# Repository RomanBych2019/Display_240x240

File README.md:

# Display 240x240

Прошивка дисплея 240x240 для системы CNG/EVO на базе ESP32-C3. Устройство читает данные автомобиля и газового блока по CAN, отображает телеметрию на TFT-дисплее, рассчитывает показатели экономичного вождения и поднимает локальный Wi-Fi веб-портал для просмотра параметров, настройки страниц дисплея, загрузки файлов и OTA-обновления.

## Возможности

- Прием CAN-данных EVO и J1939: обороты, скорость, пробег, расход ДТ, температуры, нагрузка двигателя, вес автомобиля, параметры CNG.
- Отображение страниц на круглом/квадратном TFT 240x240: CNG, параметры EVO, кнопка газ/ДТ, уровень топлива, соленоиды, потеря связи с EVO.
- Переключение пользовательских страниц жестами тач-контроллера CST816D.
- Долгое нажатие на странице кнопки газ/ДТ отправляет CAN-команду включения/выключения газа.
- Расчет уровня экономичного вождения по карте `ACC/RPM`.
- Расчет среднего расхода газа и примерного остаточного пробега.
- Веб-портал в режиме Wi-Fi AP для телеметрии и настроек.
- OTA-обновление через GyverPortal.
- Контроль перегрева ESP32: при высокой температуре снижается мощность Wi-Fi, частота обновления и яркость дисплея.

## Аппаратная платформа

- MCU: `ESP32-C3 DevKitM-1`
- Framework: Arduino
- Дисплей: TFT 240x240, драйвер `GC9A01`, библиотека `TFT_eSPI`
- Тач-контроллер: `CST816D`
- CAN: TWAI ESP32-C3, библиотека `ESP32-TWAI-CAN`
- Файловая система: `LittleFS`

### Основные пины

| Узел | Сигнал | GPIO |
| --- | --- | --- |
| CAN | RX | `GPIO20` |
| CAN | TX | `GPIO21` |
| Touch I2C | SDA | `GPIO4` |
| Touch I2C | SCL | `GPIO5` |
| Touch | INT | `GPIO0` |
| Touch | RST | `GPIO1` |
| TFT SPI | MOSI | `GPIO7` |
| TFT SPI | SCLK | `GPIO6` |
| TFT | CS | `GPIO10` |
| TFT | DC | `GPIO2` |
| TFT | BL | `GPIO3` |
| TFT | RST | `-1` |

Пины TFT задаются в локальной копии библиотеки: `lib/TFT_eSPI-master/User_Setup.h`.

## Сборка и прошивка

Проект собирается через PlatformIO.

```bash
pio run
```

Загрузка прошивки:

```bash
pio run --target upload
```

Загрузка файлов LittleFS из папки `data/`:

```bash
pio run --target uploadfs
```

Монитор порта:

```bash
pio device monitor
```

Основное окружение PlatformIO:

- `env:esp32-c3-devkitm-1`
- `platform = espressif32@5.3.0`
- `board = esp32-c3-devkitm-1`
- `framework = arduino`
- `board_build.partitions = partition.csv`
- `board_build.filesystem = littlefs`
- `monitor_speed = 115200`
- USB CDC включен на старте через `ARDUINO_USB_CDC_ON_BOOT=1`

## Wi-Fi и веб-портал

После запуска устройство поднимает точку доступа:

- SSID: `DisplayEVO`
- Пароль: `00000001`

Веб-портал построен на `GyverPortal`. Через него доступны:

- вкладка телеметрии автомобиля и EVO;
- выбор скорости CAN-шины;
- выбор типа автомобиля;
- настройка объема газовых баллонов;
- включение/отключение страниц дисплея;
- загрузка карты `Map_ACC-RPM.csv`;
- OTA-обновление.

Данные для OTA:

- Логин: `ItalGaz`
- Пароль: `001`

## Файлы LittleFS

Содержимое папки `data/` загружается во flash-файловую систему устройства.

| Файл | Назначение |
| --- | --- |
| `Map_ACC-RPM.csv` | Карта оценки экономичности по педали ACC и RPM |
| `Error_EVO_new.csv` | Справочник ошибок EVO |
| `screen*.png` | PNG-экраны/графика для отображения |
| `display_config.json` | Настройки дисплея и автомобиля, создаются/обновляются прошивкой |

Если `display_config.json` отсутствует, прошивка использует значения по умолчанию из `src/main.cpp` и `src/can_settings.h`.

## CAN-данные

Прошивка принимает расширенные CAN-кадры EVO и стандартные J1939 PGN автомобиля. Основные идентификаторы описаны в `src/can_settings.h`.

### Входящие EVO

| ID | Назначение |
| --- | --- |
| `0x18FFF0BB` | состояние газ/ДТ, ACC, впрыск газа, давление, температуры |
| `0x18FFF1BB` | уровень CNG и температура редуктора |
| `0x18FFFBBB` | ошибки EVO и версия |
| `0x18FFF8BB` | расход газа за поездку и общий расход |
| `0x18FFFAA1` | состояние и токи соленоидов |
| `0x18FFFBA1` | уровень дизельного топлива |

### Входящие J1939

| PGN | Назначение |
| --- | --- |
| `0xFEF1` | скорость автомобиля |
| `0xFEC1` | пробег |
| `0xFEF2` | мгновенный расход ДТ |
| `0xF004` | обороты и нагрузка двигателя |
| `0xFEF6` | температуры воздуха/выхлопа |
| `0xFEEE` | температуры ОЖ, масла, топлива |
| `0xFEEA` | вес автомобиля |

### Исходящие CAN

| ID | Назначение |
| --- | --- |
| `0x18FFEEDD` | команда включения/выключения газа |
| `0x18FFFEDD` | диагностические данные дисплея: экономичность, средний расход, запас хода, объем баллонов |

## Структура проекта

```text
.
├── data/                  # файлы LittleFS
├── display/               # графические исходники дисплея
├── docs/                  # документация, схемы, платы, даташиты
├── include/               # стандартная папка PlatformIO
├── lib/                   # локальные библиотеки проекта
├── src/                   # исходный код прошивки
├── test/                  # стандартная папка PlatformIO
├── platformio.ini         # настройки сборки
├── partition.csv          # разметка flash
├── max_app_4MB.csv        # альтернативная разметка
└── min_spiffs.csv         # альтернативная разметка
```

Ключевые файлы в `src/`:

- `main.cpp`, `main.h` - запуск, задачи FreeRTOS, обработка CAN, расчеты, LittleFS-настройки.
- `TFT_240_240.cpp`, `TFT_240_240.h` - отрисовка страниц TFT-дисплея.
- `WebPortal.cpp`, `WebPortal.h` - Wi-Fi AP, веб-интерфейс, OTA, загрузка файлов.
- `CST816D.cpp`, `CST816D.h` - работа с тач-контроллером.
- `can_settings.h` - структура CAN-данных и PGN/ID.
- `DisplayConfig.h` - описание страниц дисплея.
- `PNG_FS_Support.cpp`, `PNG_FS_Support.h` - вывод PNG из файловой системы.
- `SolenoidHealth.h` - состояния соленоидов.

## Локальные библиотеки

В проекте используются локальные копии библиотек:

- `lib/TFT_eSPI-master`
- `lib/PNGdec-master`
- `lib/ESP32-TWAI-CAN-master`

Также через `platformio.ini` подтягиваются:

- `gyverlibs/GyverPortal@^3.6.6`
- `bblanchon/ArduinoJson`

## Настройка страниц дисплея

Начальная конфигурация страниц задается в `src/main.cpp` в объекте `g_displayConfig`.

Доступные страницы:

- `CNG`
- `Параметры EVO`
- `Кнопка газ/дт`
- `Уровень топлива`
- `Соленоиды`
- `EVO Lost`

Веб-портал может включать и отключать пользовательские страницы. Системная страница `EVO Lost` используется для индикации потери связи с газовым блоком.

## Документация

Папка `docs/` содержит схемы, KiCad-проект платы, даташиты и инструкции. Наиболее полезные материалы:

- `docs/Инструкция.pdf`
- `docs/Инструкция карты.pdf`
- `docs/KiCad - TTF 240х240/`
- `docs/SPEC LH128R-IG01 VER A.pdf`
- `docs/esp32-c3_datasheet_en.pdf`

## Примечания для разработки

- Перед проверкой работы на устройстве прошивайте и firmware, и LittleFS.
- При изменении пинов дисплея правьте `lib/TFT_eSPI-master/User_Setup.h`.
- При изменении формата CAN-данных сначала обновляйте `src/can_settings.h`, затем парсинг в `analise_can_id()`.
- Для настройки жестов не удаляйте лог `Touch: x=..., y=..., gesture=...` в `src/main.cpp`: он нужен для проверки координат и распознавания жестов.
- В репозитории есть `.DS_Store` и `Thumbs.db`; они не нужны для сборки.

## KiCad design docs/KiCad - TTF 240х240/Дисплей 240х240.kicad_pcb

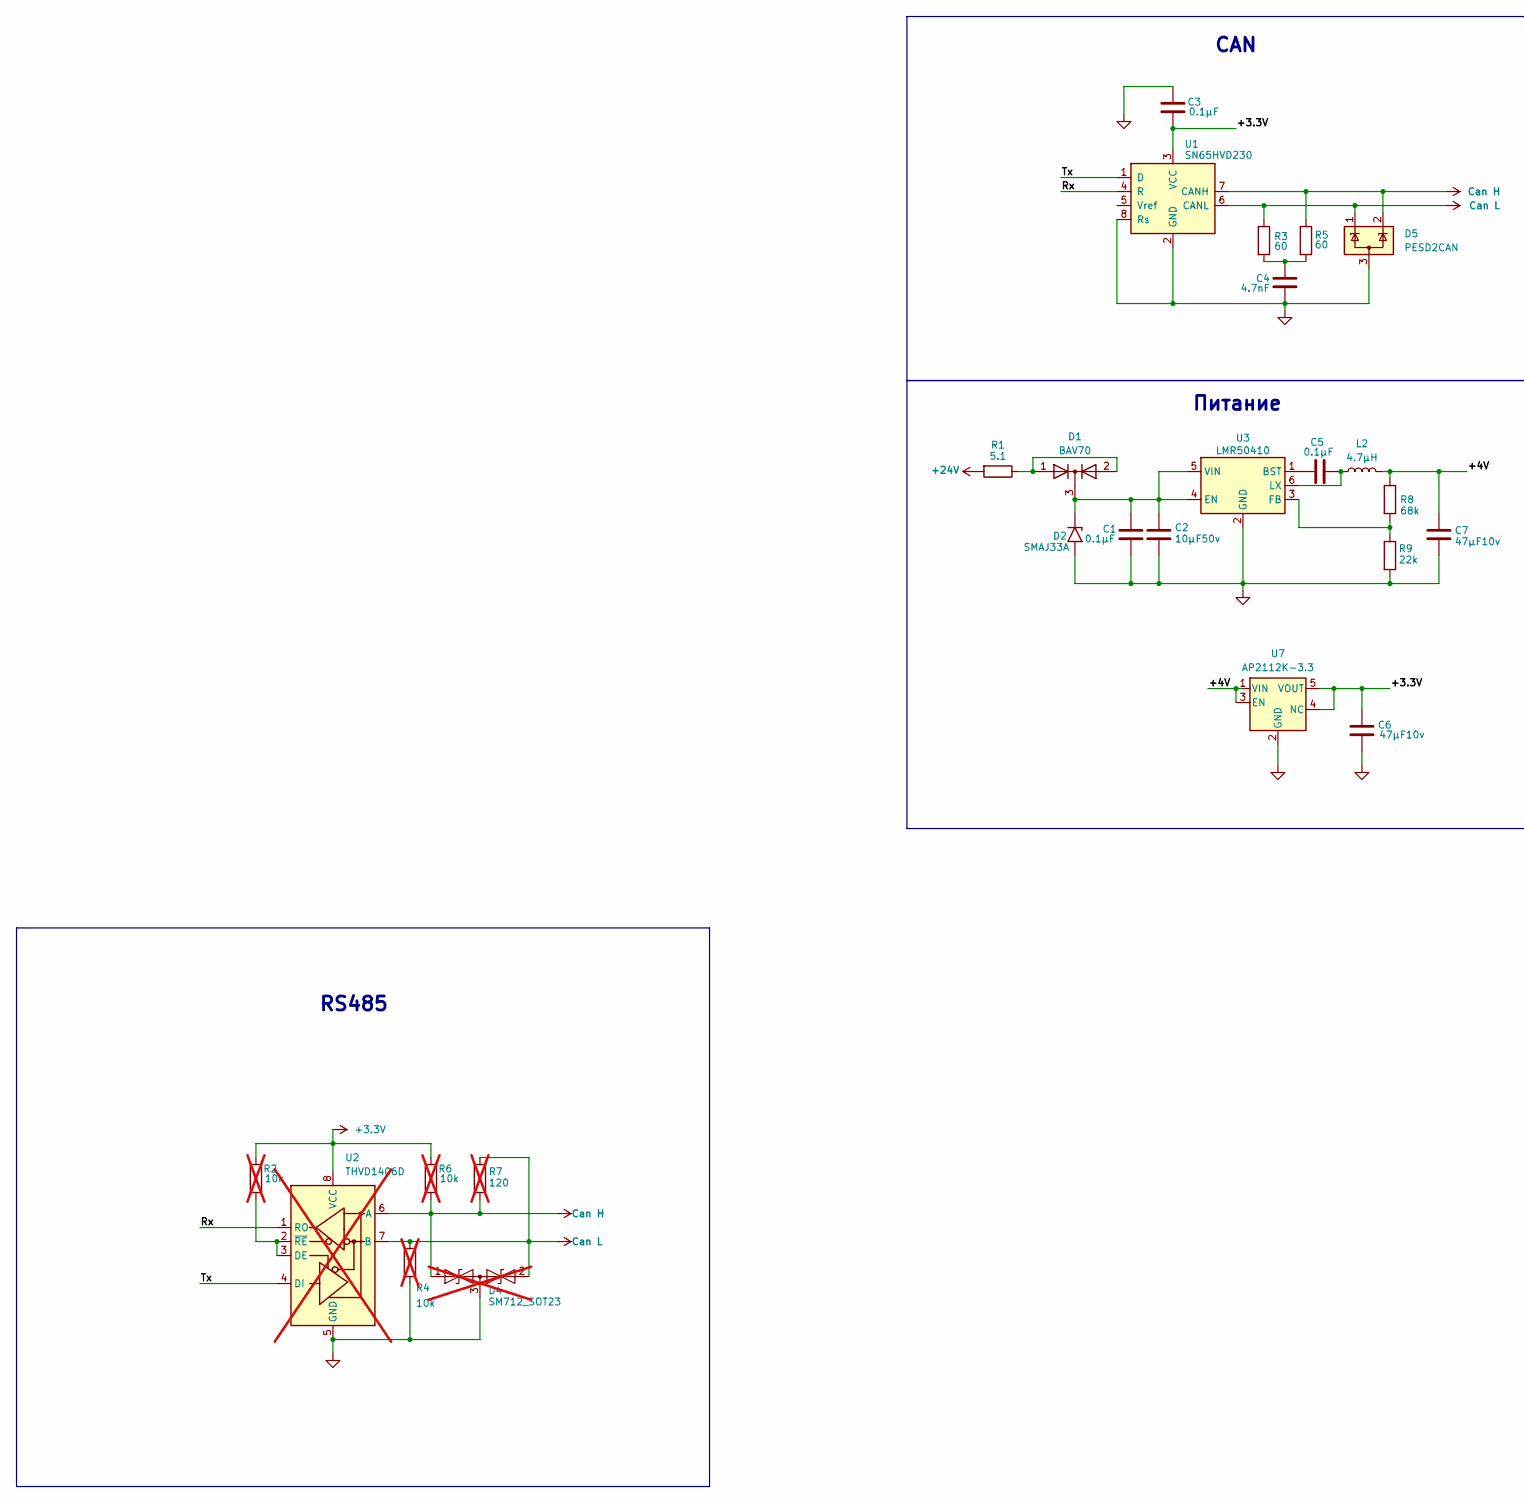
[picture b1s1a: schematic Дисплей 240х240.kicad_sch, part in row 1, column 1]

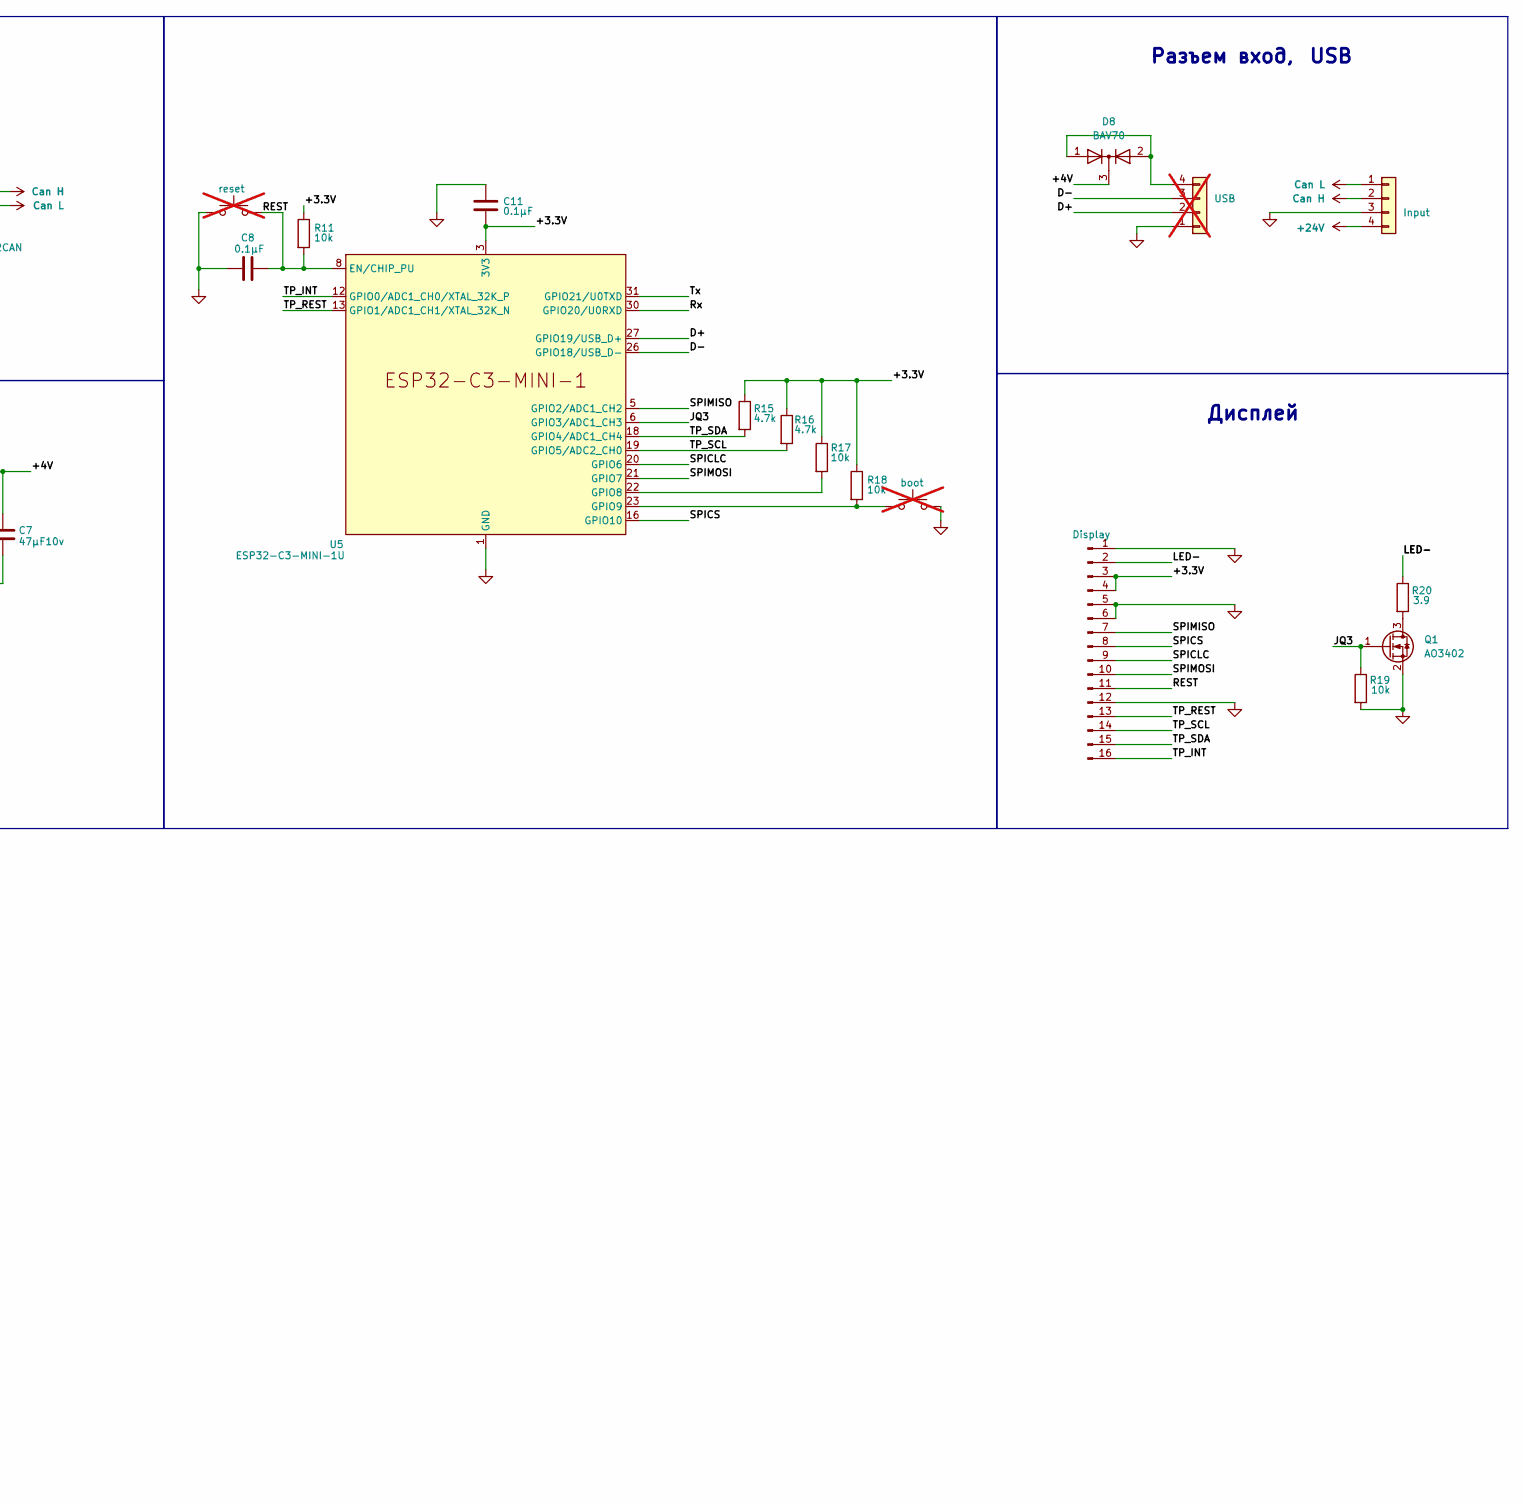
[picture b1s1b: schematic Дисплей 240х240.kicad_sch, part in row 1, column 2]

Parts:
C1, C3, C5, C8, C11: 0.1µF; C_0603_1608Metric
C2: 10µF50v; C_0805_2012Metric
C4: 4.7nF; C_0603_1608Metric
C6, C7: 47µF10v; C_0805_2012Metric
D1, D8: BAV70; SOT-23
D2: SMAJ33A; D_SMA
D4: SM712_SOT23; SOT-23; not fitted
D5: PESD2CAN; SOT-23
J1: Display; ER-OLED0.42
J2: USB; PinHeader_1x04_P2.54mm_Vertical; not fitted
J3: Input; JST_GH_BM04B-GHS-TBT_1x04-1MP_P1.25mm_Vertical
L2: 4.7µH; L_1210_3225Metric
Q1: AO3402; SOT-23
R1: 5.1; R_0805_2012Metric
R2, R4, R6: 10k; R_0603_1608Metric; not fitted
R3, R5: 60; R_0603_1608Metric
R7: 120; R_0603_1608Metric; not fitted
R8: 68k; R_0603_1608Metric
R9: 22k; R_0603_1608Metric
R11, R17, R18, R19: 10k; R_0603_1608Metric
R15, R16: 4.7k; R_0603_1608Metric
R20: 3.9; R_0603_1608Metric
SW1: reset; SW_SPST_B3U-1000P; not fitted
SW2: boot; SW_SPST_B3U-1000P; not fitted
U1: SN65HVD230; SOIC-8_3.9x4.9mm_P1.27mm
U2: THVD1406D; SOIC-8_3.9x4.9mm_P1.27mm; not fitted
U3: LMR50410; SOT-23-6
U5: ESP32-C3-MINI-1U
U7: AP2112K-3.3; SOT-23-5

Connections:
+3.3V: C3.1, C6.1, C11.1, J1.3, J1.4, R2.1, R6.1, R11.1, R15.1, R16.1, R17.1, R18.1, U1.3 (VCC), U2.8 (VCC), U5.3 (3V3), U7.4 (NC), U7.5 (VOUT)
+24V: J3.4, R1.2
/+4V: C7.1, D8.3 (K), L2.2, R8.1, U7.1 (VIN), U7.3 (EN)
/<NO NET>: U1.1 (D), U1.4 (R), U2.1 (RO), U2.4 (DI), U5.30 (GPIO20/U0RXD), U5.31 (GPIO21/U0TXD)
/D+: J2.2, U5.27 (GPIO19/USB_D+)
/D-: J2.3, U5.26 (GPIO18/USB_D-)
/JQ3: Q1.1 (G), R19.1, U5.6 (GPIO3/ADC1_CH3)
/LED-: J1.2, R20.1
/REST: C8.1, J1.11, R11.2, SW1.2, U5.8 (EN/CHIP_PU)
/SPICLC: J1.9, U5.20 (GPIO6)
/SPICS: J1.8, U5.16 (GPIO10)
/SPIMISO: J1.7, U5.5 (GPIO2/ADC1_CH2)
/SPIMOSI: J1.10, U5.21 (GPIO7)
/TP_INT: J1.16, U5.12 (GPIO0/ADC1_CH0/XTAL_32K_P)
/TP_REST: J1.13, U5.13 (GPIO1/ADC1_CH1/XTAL_32K_N)
/TP_SCL: J1.14, R16.2, U5.19 (GPIO5/ADC2_CH0)
/TP_SDA: J1.15, R15.2, U5.18 (GPIO4/ADC1_CH4)
Can H: D4.1 (A1), D5.2 (K), J3.2, R5.1, R6.2, R7.2, U1.7 (CANH), U2.6 (A)
Can L: D4.2 (A2), D5.1 (K), J3.1, R3.1, R4.1, R7.1, U1.6 (CANL), U2.7 (B)
GND: C1.2, C2.2, C3.2, C4.1, C6.2, C7.2, C8.2, C11.2, D2.2 (A2), D4.3 (common), D5.3 (A), J1.1, J1.5, J1.6, J1.12, J2.1, J3.3, Q1.2 (S), R4.2, R9.2, R19.2, SW1.1, SW2.2, U1.2 (GND), U1.8 (Rs), U2.5 (GND), U3.2 (GND), U5.1 (GND), U5.2 (GND), U5.11 (GND), U5.14 (GND), U5.36 (GND), U5.37 (GND), U5.38 (GND), U5.39 (GND), U5.40 (GND), U5.41 (GND), U5.42 (GND), U5.43 (GND), U5.44 (GND), U5.45 (GND), U5.46 (GND), U5.47 (GND), U5.48 (GND), U5.49 (GND), U5.50 (GND), U5.51 (GND), U5.52 (GND), U5.53 (GND), U7.2 (GND)
unnamed: C4.2, R3.2, R5.2
unnamed: D1.1 (A), D1.2 (A), R1.1
unnamed: C1.1, C2.1, D1.3 (K), D2.1 (A1), U3.4 (EN), U3.5 (VIN)
unnamed: D8.1 (A), D8.2 (A), J2.4
unnamed: Q1.3 (D), R20.2
unnamed: R2.2, U2.2 (~RE), U2.3 (DE)
unnamed: C5.2, U3.1 (BST)
unnamed: R8.2, R9.1, U3.3 (FB)
unnamed: C5.1, L2.1, U3.6 (LX)
unnamed: R17.2, U5.22 (GPIO8)
unnamed: R18.2, SW2.1, U5.23 (GPIO9)

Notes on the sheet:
Питание
Дисплей
CAN
RS485
Разъем вход, USB

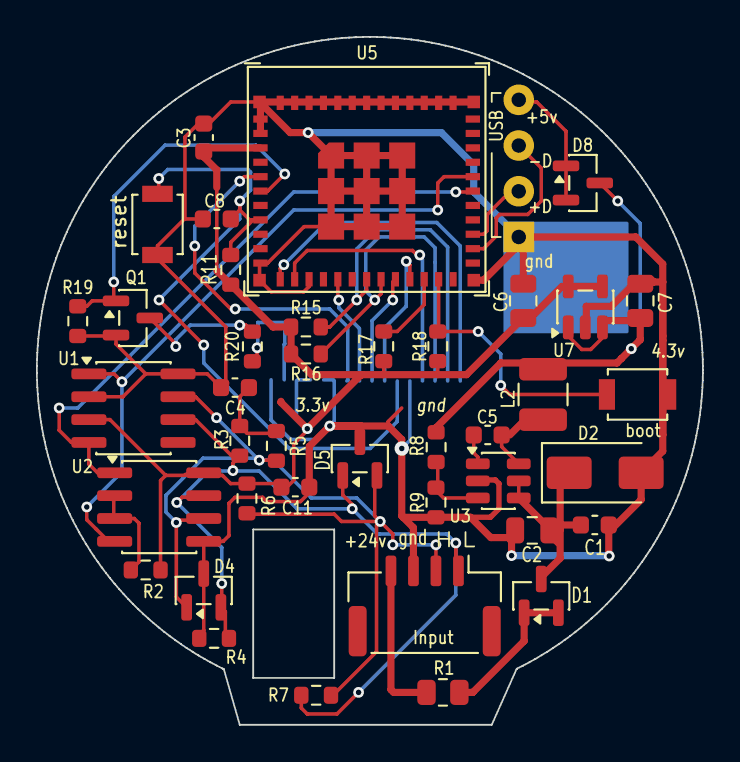
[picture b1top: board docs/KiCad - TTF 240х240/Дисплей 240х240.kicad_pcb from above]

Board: 2 copper layers, 37.0 x 38.2 mm, 42 parts (1 on the bottom side), 31 nets.

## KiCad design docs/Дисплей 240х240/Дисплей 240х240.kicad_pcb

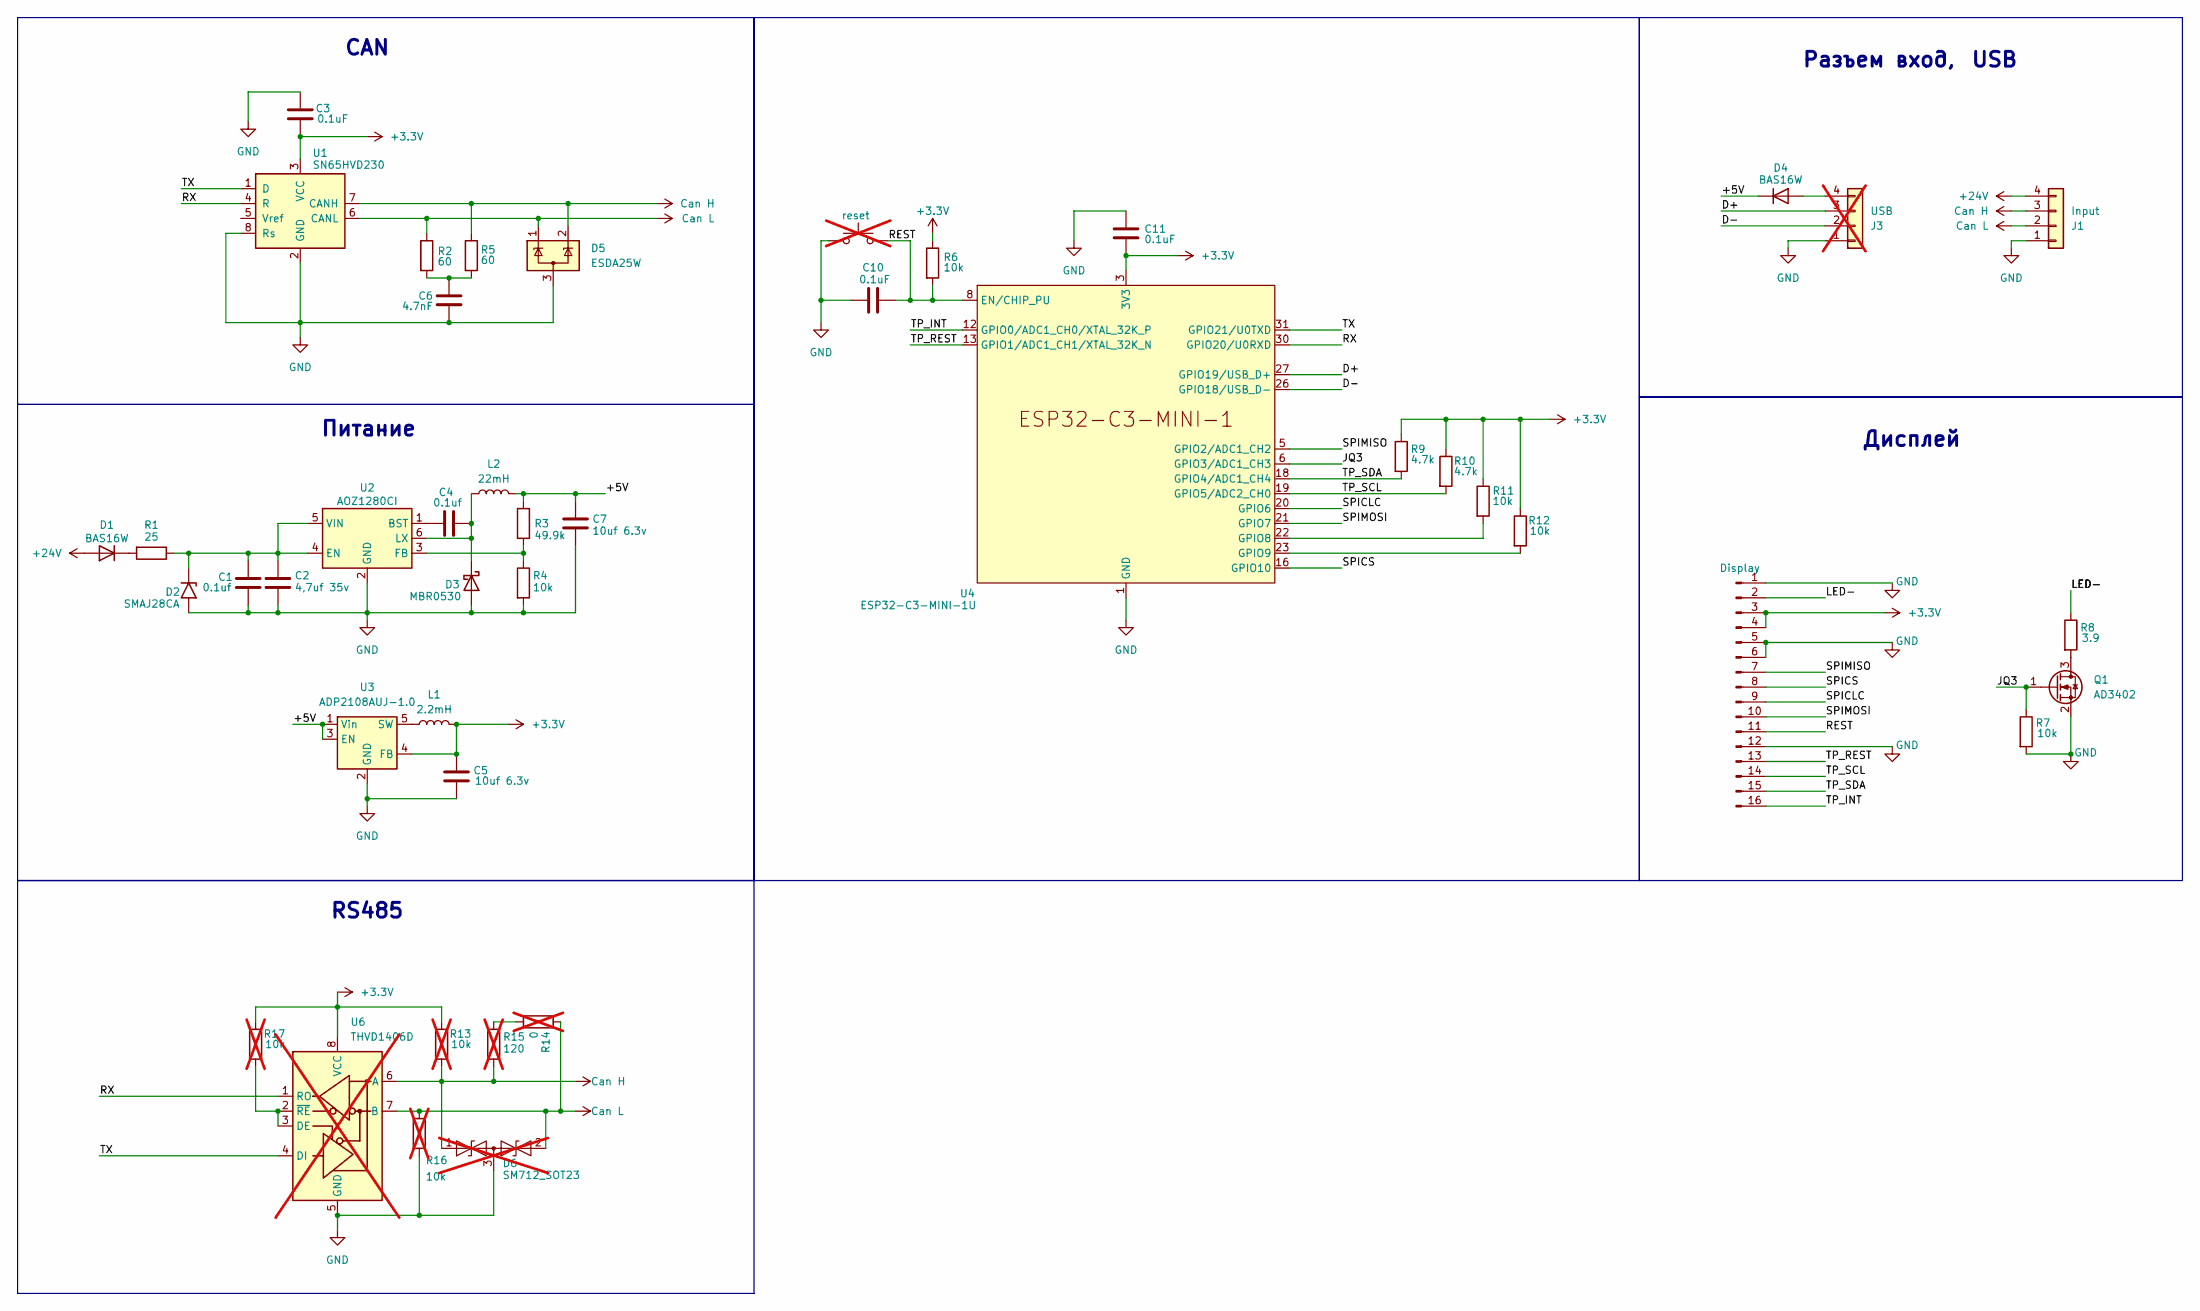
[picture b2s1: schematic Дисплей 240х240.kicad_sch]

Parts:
C1, C4: 0.1uf; C_0603_1608Metric
C2: 4,7uf 35v; CP_EIA-3528-21_Kemet-B
C3, C10, C11: 0.1uF; C_0603_1608Metric
C5, C7: 10uf 6.3v; CP_EIA-3216-18_Kemet-A
C6: 4.7nF; C_0603_1608Metric
D1, D4: BAS16W; SOT-323_SC-70
D2: SMAJ28CA; D_SMA
D3: MBR0530; D_SOD-123
D5: ESDA25W; SOT-23-3
D6: SM712_SOT23; SOT-23; not fitted
J1: Input; JST_GH_BM04B-GHS-TBT_1x04-1MP_P1.25mm_Vertical
J2: Display; ER-OLED0.42-1W_Folded
J3: USB; PinHeader_1x04_P2.54mm_Vertical; not fitted
L1: 2.2mH; L_1206_3216Metric
L2: 22mH; L_1210_3225Metric
Q1: AD3402; SOT-23
R1: 25; Fuse_0805_2012Metric
R2, R5: 60; R_0603_1608Metric
R3: 49.9k; R_0603_1608Metric
R4, R6, R7, R11, R12: 10k; R_0603_1608Metric
R8: 3.9; R_0603_1608Metric
R9, R10: 4.7k; R_0603_1608Metric
R13, R16, R17: 10k; R_0603_1608Metric; not fitted
R14: 0; R_0603_1608Metric; not fitted
R15: 120; R_0603_1608Metric; not fitted
SW1: reset; SW_SPST_B3U-1000P; not fitted
U1: SN65HVD230; SOIC-8_3.9x4.9mm_P1.27mm
U2: AOZ1280CI; SOT-23-6
U3: ADP2108AUJ-1.0; TSOT-23-5
U4: ESP32-C3-MINI-1U
U6: THVD1406D; SOIC-8_3.9x4.9mm_P1.27mm; not fitted

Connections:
+3.3V: C3.1, C5.1, C11.1, J2.3, J2.4, L1.2, R6.1, R9.1, R10.1, R11.1, R12.1, R13.1, R17.1, U1.3 (VCC), U3.4 (FB), U4.3 (3V3), U6.8 (VCC)
+24V: D1.1 (A), J1.4
/+5V: C7.1, D4.3 (K), L2.2, R3.1, U3.1 (Vin), U3.3 (EN)
/D+: J3.3, U4.27 (GPIO19/USB_D+)
/D-: J3.2, U4.26 (GPIO18/USB_D-)
/JQ3: Q1.1 (G), R7.1, U4.6 (GPIO3/ADC1_CH3)
/LED-: J2.2, R8.1
/REST: C10.1, J2.11, R6.2, SW1.2, U4.8 (EN/CHIP_PU)
/SPICLC: J2.9, U4.20 (GPIO6)
/SPICS: J2.8, U4.16 (GPIO10)
/SPIMISO: J2.7, U4.5 (GPIO2/ADC1_CH2)
/SPIMOSI: J2.10, U4.21 (GPIO7)
/TP_INT: J2.16, U4.12 (GPIO0/ADC1_CH0/XTAL_32K_P)
/TP_REST: J2.13, U4.13 (GPIO1/ADC1_CH1/XTAL_32K_N)
/TP_SCL: J2.14, R10.2, U4.19 (GPIO5/ADC2_CH0)
/TP_SDA: J2.15, R9.2, U4.18 (GPIO4/ADC1_CH4)
Can H: D5.2 (K), D6.1 (A1), J1.3, R5.1, R13.2, R15.2, U1.7 (CANH), U6.6 (A)
Can L: D5.1 (K), D6.2 (A2), J1.2, R2.1, R14.1, R16.1, U1.6 (CANL), U6.7 (B)
GND: C1.2, C2.2, C3.2, C5.2, C6.1, C7.2, C10.2, C11.2, D2.2 (A2), D3.2 (A), D5.3 (A), D6.3 (common), J1.1, J2.1, J2.5, J2.6, J2.12, J3.1, Q1.2 (S), R4.2, R7.2, R16.2, SW1.1, U1.2 (GND), U1.8 (Rs), U2.2 (GND), U3.2 (GND), U4.1 (GND), U4.2 (GND), U4.11 (GND), U4.14 (GND), U4.36 (GND), U4.37 (GND), U4.38 (GND), U4.39 (GND), U4.40 (GND), U4.41 (GND), U4.42 (GND), U4.43 (GND), U4.44 (GND), U4.45 (GND), U4.46 (GND), U4.47 (GND), U4.48 (GND), U4.49 (GND), U4.50 (GND), U4.51 (GND), U4.52 (GND), U4.53 (GND), U6.5 (GND)
unnamed: C6.2, R2.2, R5.2
unnamed: D1.3 (K), R1.2
unnamed: C1.1, C2.1, D2.1 (A1), R1.1, U2.4 (EN), U2.5 (VIN)
unnamed: C4.1, D3.1 (K), L2.1, U2.6 (LX)
unnamed: D4.1 (A), J3.4
unnamed: Q1.3 (D), R8.2
unnamed: R14.2, R15.1
unnamed: C4.2, U2.1 (BST)
unnamed: R3.2, R4.1, U2.3 (FB)
unnamed: L1.1, U3.5 (SW)
unnamed: R11.2, U4.22 (GPIO8)
unnamed: R12.2, U4.23 (GPIO9)
unnamed: R17.2, U6.2 (~RE), U6.3 (DE)

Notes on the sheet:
Питание
Дисплей
CAN
RS485
Разъем вход, USB

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
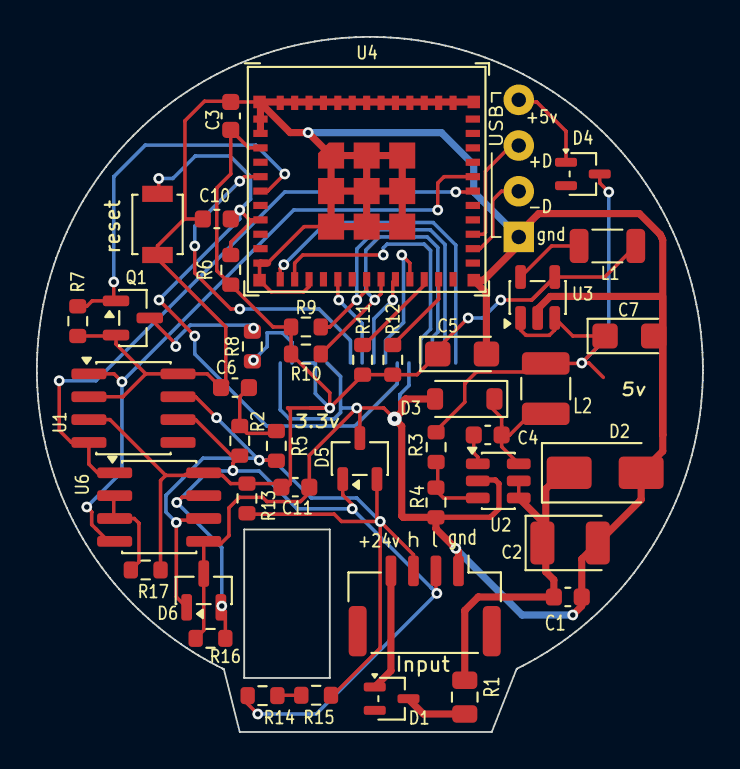
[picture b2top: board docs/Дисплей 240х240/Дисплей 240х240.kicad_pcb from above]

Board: 2 copper layers, 37.0 x 38.6 mm, 44 parts (1 on the bottom side), 34 nets.

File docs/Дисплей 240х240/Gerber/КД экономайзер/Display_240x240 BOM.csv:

Идентиф.;Обозначение;Посад. место;Количество;Значение;Поставщик и справка;;
1;D2;D_SMA;1;SMAJ30CA;;;
2;D6;SOT-23;1;SM712_SOT23;;;
3;C3,C10,C11;C_0603_1608Metric;3;0.1uF;;;
4;C7,C5;CP_EIA-3216-18_Kemet-A;2;10uf 6.3v;;;
5;U1;SOIC-8_3.9x4.9mm_P1.27mm;1;SN65HVD230;;;
6;SW1;SW_SPST_B3U-1000P;1;reset;;;
7;R4;R_0603_1608Metric;1;49.9k;;;
8;R15;R_0603_1608Metric;1;120;;;
9;L1;L_1206_3216Metric;1;2.2mH;;;
10;R5,R2;R_0603_1608Metric;2;60;;;
11;R8;R_0603_1608Metric;1;3.9;;;
12;R1;Fuse_0805_2012Metric;1;25;;;
13;J1;JST_GH_BM04B-GHS-TBT_1x04-1MP_P1.25mm_Vertical;1;JST_GH_BM04B-GHS-TBT_1x04-1MP_P1.25mm_Vertical;;;
14;D1,D4;SOT-323_SC-70;2;BAS16W;;;
15;C2;CP_EIA-3528-21_Kemet-B;1;4,7uf 35v;;;
16;Q1;SOT-23;1;AD3402;;;
17;R11,R6,R12,R16,R7,R13,R17,R3;R_0603_1608Metric;8;10k;;;
18;R14;R_0603_1608Metric;1;0;;;
19;J3;;1;;;;
20;U4;ESP32-C3-MINI-1U;1;ESP32-C3-MINI-1U;;;
21;L2;L_1210_3225Metric;1;22mH;;;
22;R10,R9;R_0603_1608Metric;2;4.7k;;;
23;C1,C4;C_0603_1608Metric;2;0.1uf;;;
24;U3;TSOT-23-5;1;ADP2108AUJ-1.0;;;
25;U2;SOT-23-6;1;AOZ1280CI;;;
26;C6;C_0603_1608Metric;1;4.7nF;;;
27;D5;SOT-23-3;1;ESDA25W;;;
28;D3;D_SOD-123;1;MBR0530;;;
29;U6;SOIC-8_3.9x4.9mm_P1.27mm;1;THVD1406D;;;
30;J2;ER-OLED0.42-1W_Folded;1;LH128R-IG01;;;
;Корпус;Использован корпус от дисплея https://aliexpress.ru/item/1005006394111588.html?spm=a2g2w.d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;;;;;

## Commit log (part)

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2025-02-23 Исправление вывода на дисплей.
2025-11-04 Убран индикатор уровня
2025-11-04 Удаление дефолтного образа прошивки
2026-03-10 Рабочий вариант 2025
2026-03-24 Добавление файла настройки станиц JSON
2026-06-01 Рабочая версия для синей платы
